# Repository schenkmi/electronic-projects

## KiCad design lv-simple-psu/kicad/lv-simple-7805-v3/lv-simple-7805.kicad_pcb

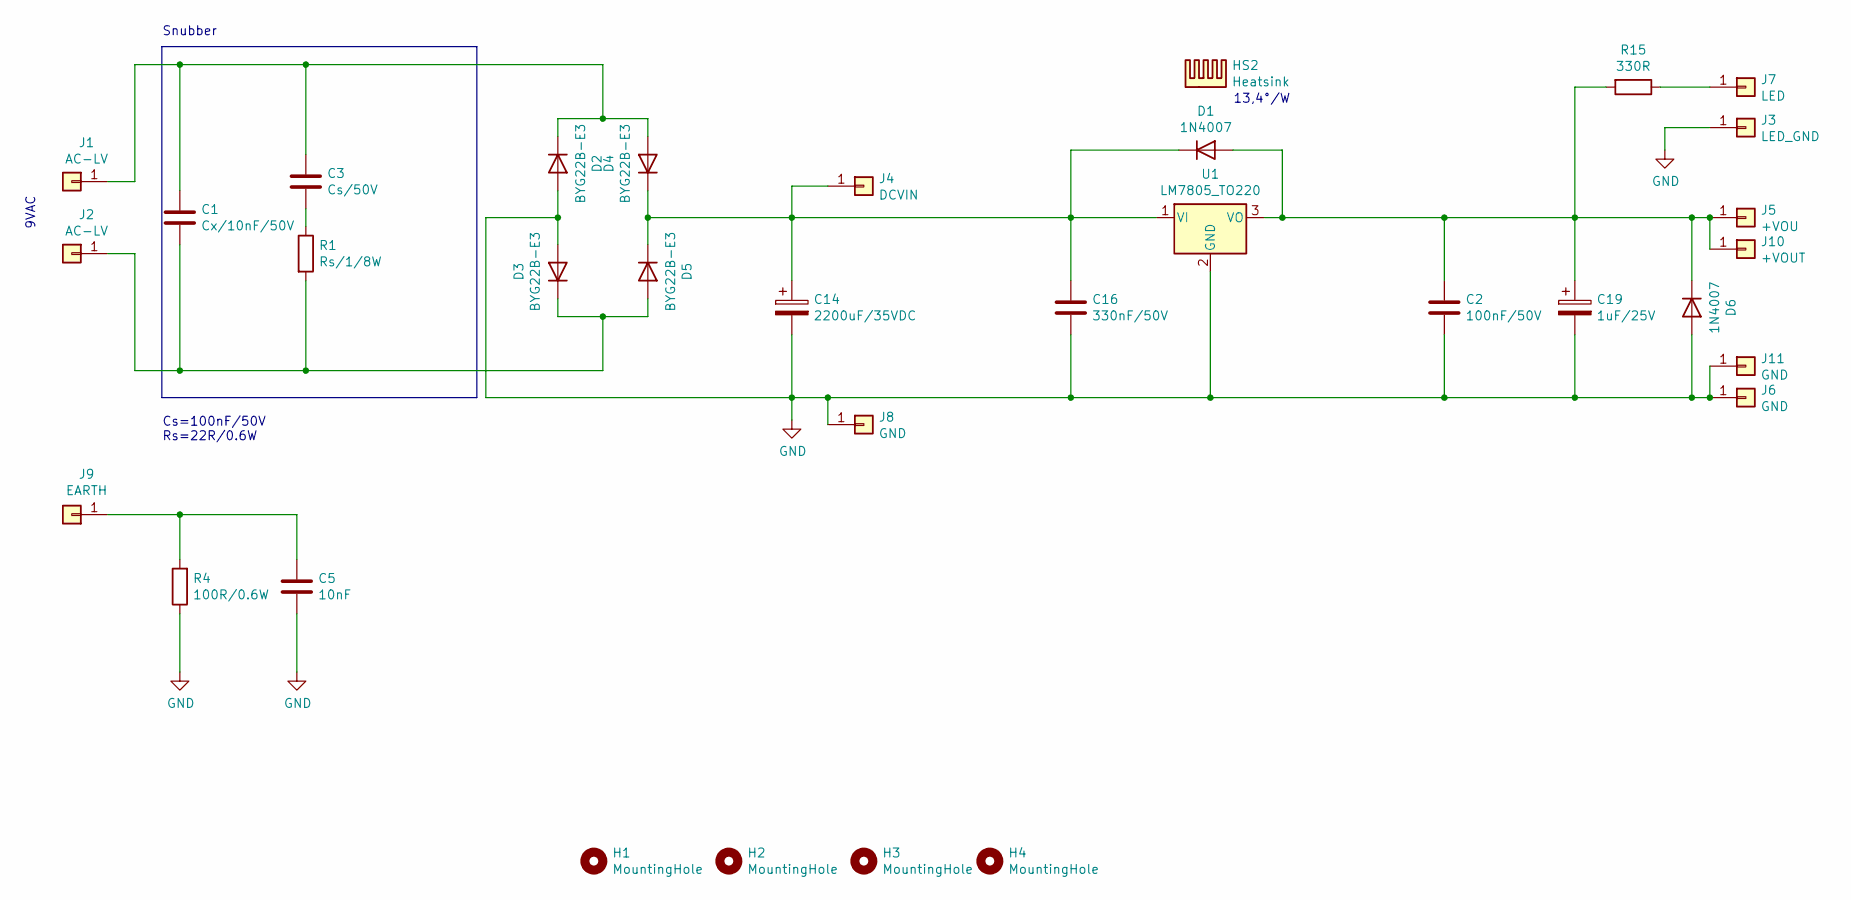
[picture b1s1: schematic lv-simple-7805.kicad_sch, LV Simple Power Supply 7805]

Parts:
C1: Cx/10nF/50V; C_0805_2012Metric_Pad1.18x1.45mm_HandSolder
C2: 100nF/50V; C_0805_2012Metric_Pad1.18x1.45mm_HandSolder
C3: Cs/50V; C_0805_2012Metric_Pad1.18x1.45mm_HandSolder
C5: 10nF; C_Rect_L7.2mm_W2.5mm_P5.00mm_FKS2_FKP2_MKS2_MKP2
C14: 2200uF/35VDC; CP_Radial_D16.0mm_P7.50mm
C16: 330nF/50V; C_0805_2012Metric_Pad1.18x1.45mm_HandSolder
C19: 1uF/25V; CP_Radial_D5.0mm_P2.00mm
D1, D6: 1N4007; D_SMA_Handsoldering
D2, D3, D4, D5: BYG22B-E3; D_SMA_Handsoldering
H1, H2, H3, H4: MountingHole; MountingHole_3.2mm_M3
HS2: Heatsink; Heatsink_Fischer_SK104-STC-STIC_35x13mm_2xDrill2.5mm
J1, J2: AC-LV; Pin_D1.3mm_L11.0mm
J3: LED_GND; Pin_D1.0mm_L10.0mm
J4: DCVIN; Pin_D1.3mm_L11.0mm
J5: +VOU; Pin_D1.3mm_L11.0mm
J6, J8: GND; Pin_D1.3mm_L11.0mm
J7: LED; Pin_D1.0mm_L10.0mm
J9: EARTH; Pin_D1.3mm_L11.0mm
J10: +VOUT; Pin_D1.0mm_L10.0mm
J11: GND; Pin_D1.0mm_L10.0mm
R1: Rs/1/8W; R_0805_2012Metric_Pad1.20x1.40mm_HandSolder
R4: 100R/0.6W; R_Axial_DIN0207_L6.3mm_D2.5mm_P10.16mm_Horizontal
R15: 330R; R_0805_2012Metric_Pad1.20x1.40mm_HandSolder
U1: LM7805_TO220; TO-220-3_Vertical

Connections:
GND: C2.2, C5.2, C14.2, C16.2, C19.2, D2.2 (A), D3.2 (A), D6.2 (A), J3.1, J6.1, J8.1, J11.1, R4.1, U1.2 (GND)
unnamed: C1.1, C3.1, D2.1 (K), D4.2 (A), J1.1
unnamed: C1.2, D3.1 (K), D5.2 (A), J2.1, R1.2
unnamed: C3.2, R1.1
unnamed: C5.1, J9.1, R4.2
unnamed: C14.1, C16.1, D1.1 (K), D4.1 (K), D5.1 (K), J4.1, U1.1 (VI)
unnamed: C2.1, C19.1, D1.2 (A), D6.1 (K), J5.1, J10.1, R15.2, U1.3 (VO)
unnamed: J7.1, R15.1

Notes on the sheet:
Snubber
9VAC
13,4°/W
Cs=100nF/50V Rs=22R/0.6W

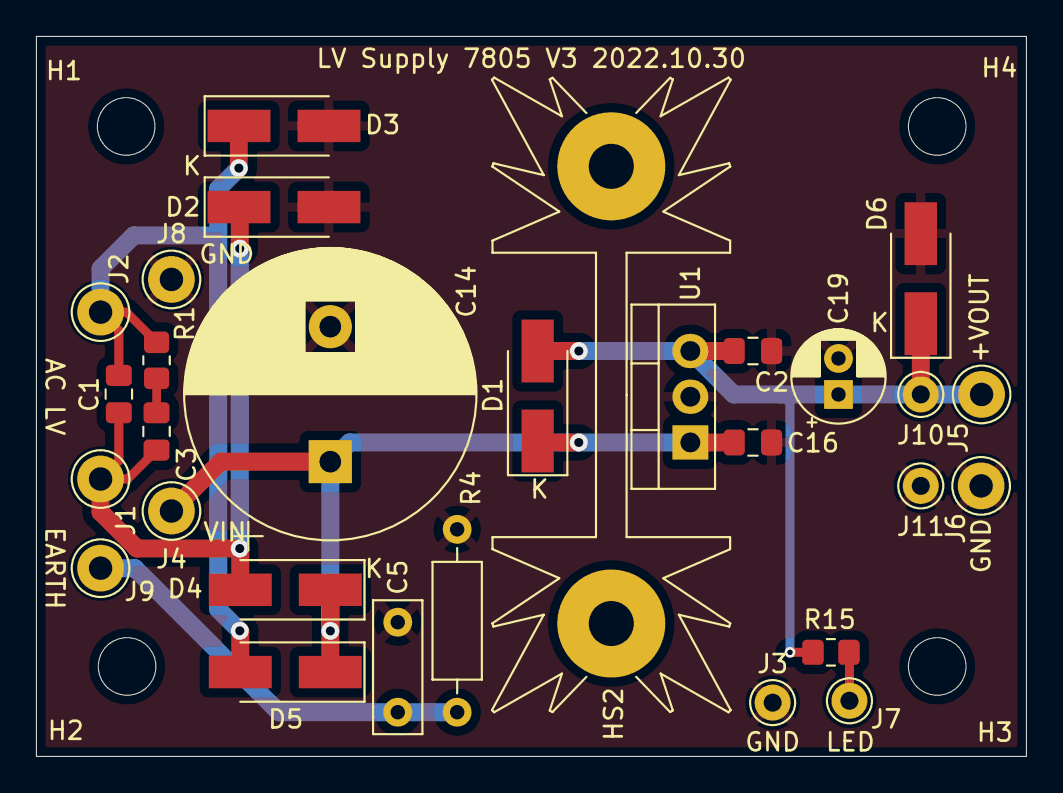
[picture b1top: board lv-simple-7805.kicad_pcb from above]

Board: 2 copper layers, 55.0 x 40.0 mm, 33 parts (0 on the bottom side), 8 nets.

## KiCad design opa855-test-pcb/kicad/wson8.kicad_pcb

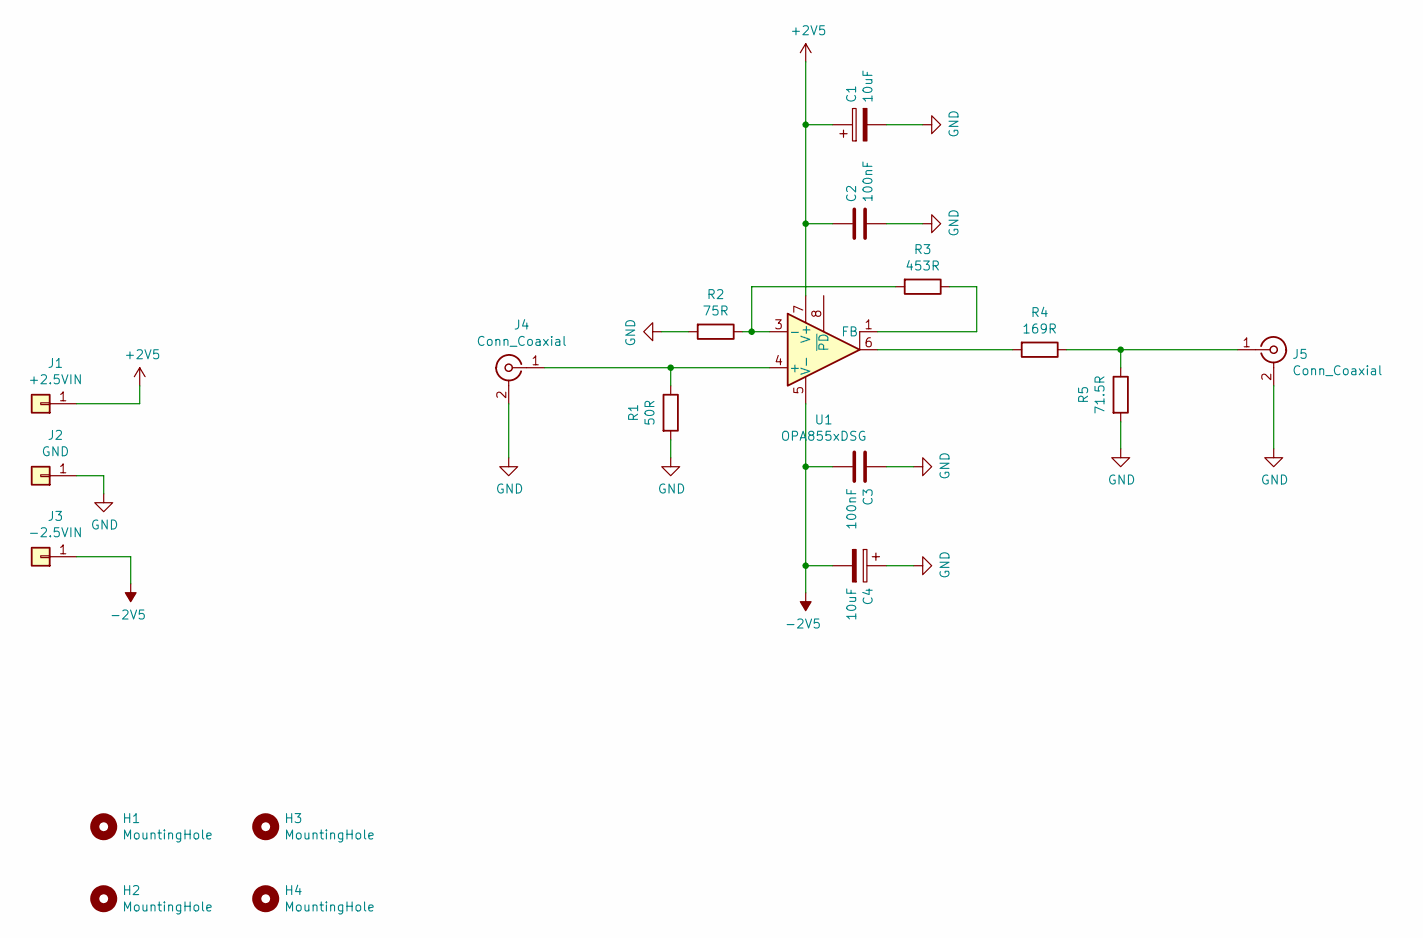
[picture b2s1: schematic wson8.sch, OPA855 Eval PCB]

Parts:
C1, C4: 10uF; CP_EIA-3528-21_Kemet-B_Pad1.50x2.35mm_HandSolder
C2, C3: 100nF; C_0603_1608Metric_Pad1.08x0.95mm_HandSolder
H1, H2, H3, H4: MountingHole; MountingHole_3.2mm_M3
J1: +2.5VIN; Pin_D1.0mm_L10.0mm
J2: GND; Pin_D1.0mm_L10.0mm
J3: -2.5VIN; Pin_D1.0mm_L10.0mm
J4, J5: Conn_Coaxial; MMCX_Molex_73415-1471_Vertical
R1: 50R; R_0603_1608Metric_Pad0.98x0.95mm_HandSolder
R2: 75R; R_0603_1608Metric_Pad0.98x0.95mm_HandSolder
R3: 453R; R_0603_1608Metric_Pad0.98x0.95mm_HandSolder
R4: 169R; R_0603_1608Metric_Pad0.98x0.95mm_HandSolder
R5: 71.5R; R_0603_1608Metric_Pad0.98x0.95mm_HandSolder
U1: OPA855xDSG; WSON-8-1EP_2x2mm_P0.5mm_EP0.9x1.6mm

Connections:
+2V5: C1.1, C2.1, J1.1, U1.7 (V+)
-2V5: C3.2, C4.2, J3.1, U1.5 (V-), U1.9 (V-)
GND: C1.2, C2.2, C3.1, C4.1, J2.1, J4.2 (Ext), J5.2 (Ext), R1.2, R2.2, R5.2
unnamed: J4.1 (In), R1.1, U1.4 (+)
unnamed: J5.1 (In), R4.1, R5.1
unnamed: R2.1, R3.2, U1.3 (-)
unnamed: R3.1, U1.1 (FB)
unnamed: R4.2, U1.6

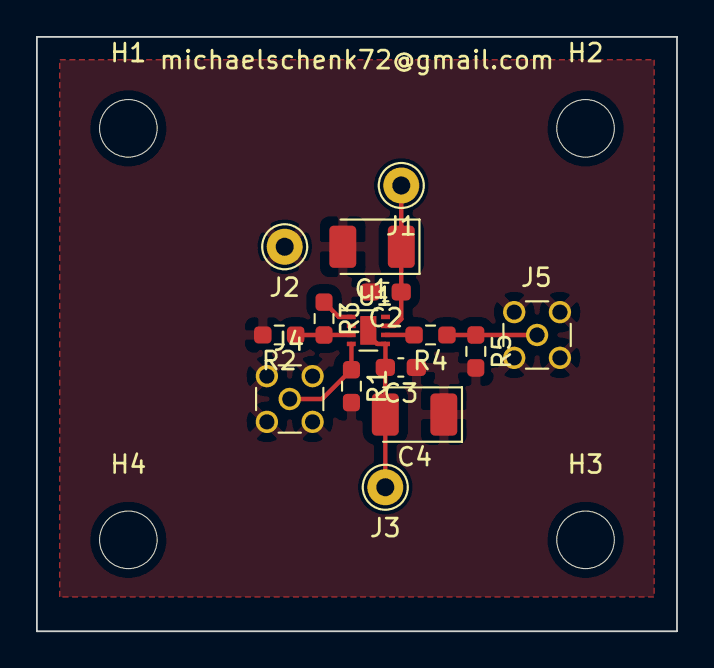
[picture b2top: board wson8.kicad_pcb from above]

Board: 2 copper layers, 35.6 x 33.0 mm, 19 parts (0 on the bottom side), 8 nets.

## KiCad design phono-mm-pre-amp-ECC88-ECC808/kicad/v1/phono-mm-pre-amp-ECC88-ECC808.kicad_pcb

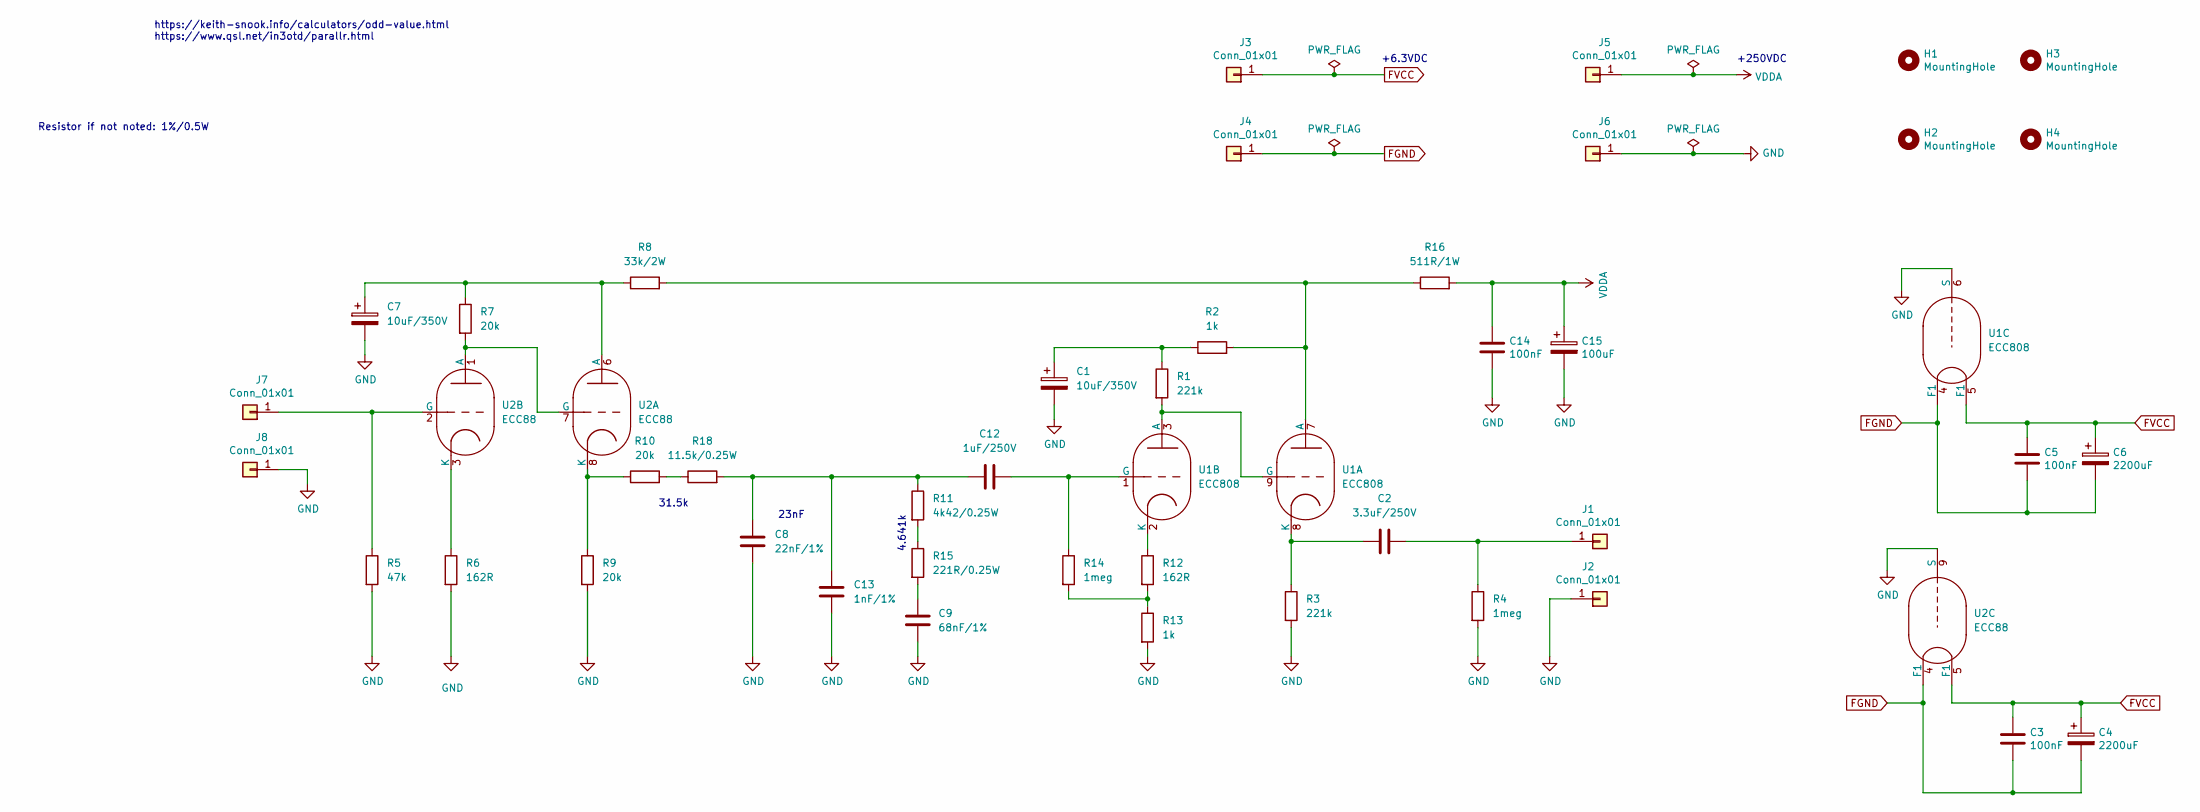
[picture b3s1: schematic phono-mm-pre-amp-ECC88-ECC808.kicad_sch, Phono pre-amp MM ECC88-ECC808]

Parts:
C1, C7: 10uF/350V; CP_Radial_D10.0mm_P5.00mm
C2: 3.3uF/250V; C_Rect_L31.5mm_W13.0mm_P27.50mm_MKS4
C3, C5: 100nF; C_Rect_L7.2mm_W2.5mm_P5.00mm_FKS2_FKP2_MKS2_MKP2
C4, C6: 2200uF; CP_Radial_D16.0mm_P7.50mm
C8: 22nF/1%; C_Rect_L7.2mm_W5.5mm_P5.00mm_FKS2_FKP2_MKS2_MKP2
C9: 68nF/1%; C_Rect_L7.2mm_W7.2mm_P5.00mm_FKS2_FKP2_MKS2_MKP2
C12: 1uF/250V; C_Rect_L26.5mm_W11.5mm_P22.50mm_MKS4
C13: 1nF/1%; C_Rect_L7.2mm_W5.5mm_P5.00mm_FKS2_FKP2_MKS2_MKP2
C14: 100nF; C_Rect_L16.5mm_W5.0mm_P15.00mm_MKT
C15: 100uF; CP_Radial_D18.0mm_P7.50mm
H1, H2, H3, H4: MountingHole; MountingHole_3.2mm_M3_Pad_Via
J1, J2, J7, J8: Conn_01x01; Pin_D1.0mm_L10.0mm
J3, J4, J5, J6: Conn_01x01; Pin_D1.3mm_L11.0mm
R1, R3: 221k; R_Axial_DIN0207_L6.3mm_D2.5mm_P10.16mm_Horizontal
R2, R13: 1k; R_Axial_DIN0207_L6.3mm_D2.5mm_P10.16mm_Horizontal
R4, R14: 1meg; R_Axial_DIN0207_L6.3mm_D2.5mm_P10.16mm_Horizontal
R5: 47k; R_Axial_DIN0207_L6.3mm_D2.5mm_P10.16mm_Horizontal
R6, R12: 162R; R_Axial_DIN0207_L6.3mm_D2.5mm_P10.16mm_Horizontal
R7, R9, R10: 20k; R_Axial_DIN0207_L6.3mm_D2.5mm_P10.16mm_Horizontal
R8: 33k/2W; R_Axial_DIN0414_L11.9mm_D4.5mm_P15.24mm_Horizontal
R11: 4k42/0.25W; R_Axial_DIN0207_L6.3mm_D2.5mm_P10.16mm_Horizontal
R15: 221R/0.25W; R_Axial_DIN0207_L6.3mm_D2.5mm_P10.16mm_Horizontal
R16: 511R/1W; R_Axial_DIN0207_L6.3mm_D2.5mm_P10.16mm_Horizontal
R18: 11.5k/0.25W; R_Axial_DIN0207_L6.3mm_D2.5mm_P10.16mm_Horizontal
U1: ECC808; TubeNoval-ECC88
U2: ECC88; TubeNoval-ECC88

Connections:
FGND: C3.2, C4.2, C5.2, C6.2, J4.1, U1.4 (F1), U2.4 (F1)
FVCC: C3.1, C4.1, C5.1, C6.1, J3.1, U1.5 (F1), U2.5 (F1)
GND: C1.2, C7.2, C8.1, C9.1, C13.1, C14.2, C15.2, J2.1, J6.1, J8.1, R3.2, R4.2, R5.2, R6.2, R9.2, R13.2, U1.6 (S), U2.9 (S)
unnamed: C1.1, R1.1, R2.1
unnamed: C9.2, R15.2
unnamed: C8.2, C12.1, C13.2, R11.1, R18.2
unnamed: C2.2, J1.1, R4.1
unnamed: J7.1, R5.1, U2.2 (G)
unnamed: R10.2, R18.1
unnamed: R11.2, R15.1
unnamed: R12.2, R13.1, R14.2
unnamed: R2.2, R8.2, R16.1, U1.7 (A)
unnamed: R1.2, U1.3 (A), U1.9 (G)
unnamed: C2.1, R3.1, U1.8 (K)
unnamed: C12.2, R14.1, U1.1 (G)
unnamed: R12.1, U1.2 (K)
unnamed: C7.1, R7.1, R8.1, U2.6 (A)
unnamed: R7.2, U2.1 (A), U2.7 (G)
unnamed: R9.1, R10.1, U2.8 (K)
unnamed: R6.1, U2.3 (K)
VDDA: C14.1, C15.1, J5.1, R16.2

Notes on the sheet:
23nF
+250VDC
4.641k
Resistor if not noted: 1%/0.5W
31.5k
https://keith-snook.info/calculators/odd-value.html https://www.qsl.net/in3otd/parallr.html
+6.3VDC

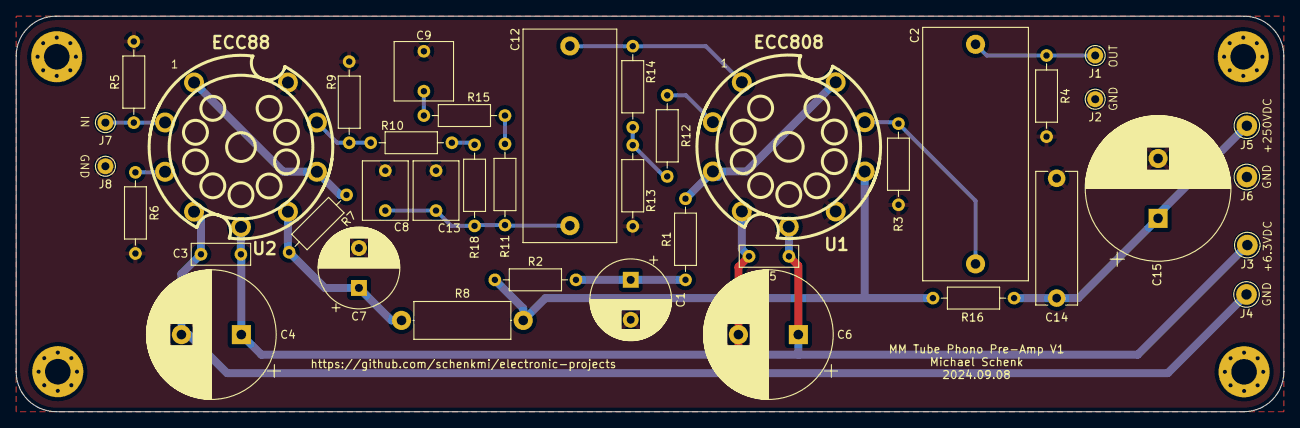
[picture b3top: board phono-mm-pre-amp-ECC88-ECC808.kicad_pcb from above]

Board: 2 copper layers, 158.8 x 49.5 mm, 44 parts (0 on the bottom side), 21 nets.

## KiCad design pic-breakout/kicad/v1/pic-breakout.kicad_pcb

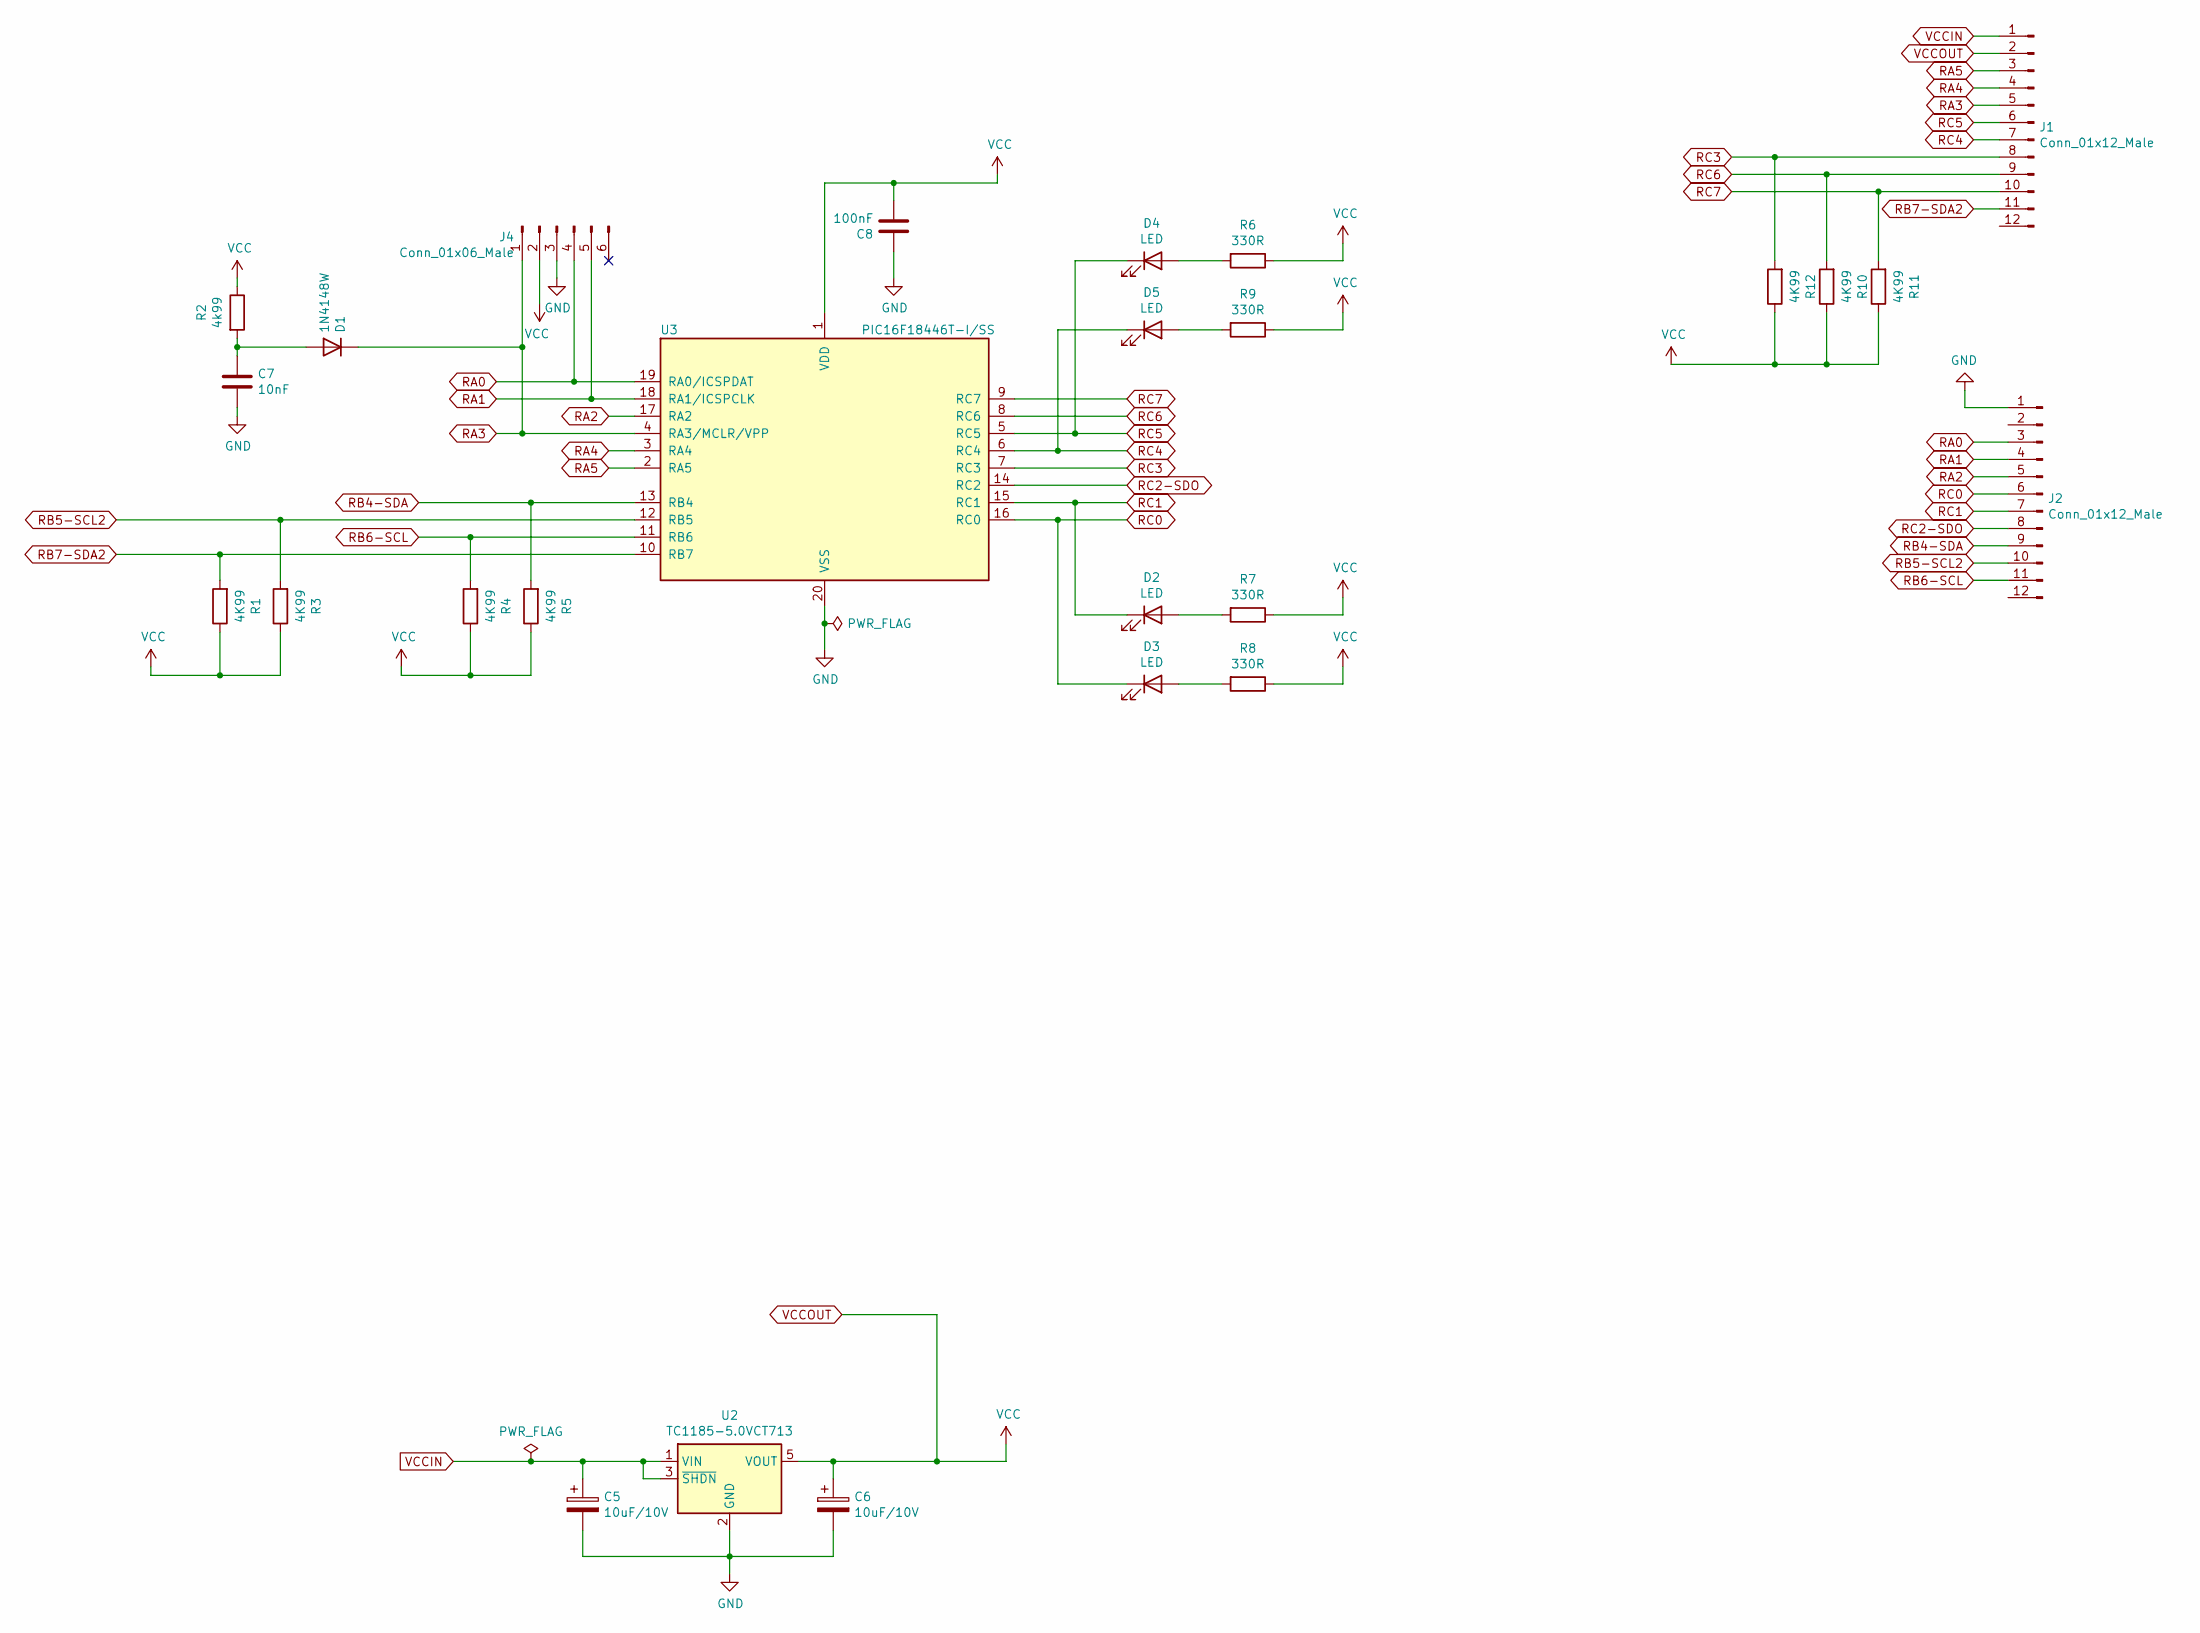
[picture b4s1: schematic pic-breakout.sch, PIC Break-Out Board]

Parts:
C5, C6: 10uF/10V; CP_EIA-2012-15_AVX-P_Pad1.30x1.05mm_HandSolder
C7: 10nF; C_0603_1608Metric_Pad1.08x0.95mm_HandSolder
C8: 100nF; C_0603_1608Metric_Pad1.08x0.95mm_HandSolder
D1: 1N4148W; D_SOD-123
D2, D3, D4, D5: LED; LED_0805_2012Metric_Pad1.15x1.40mm_HandSolder
J1, J2: Conn_01x12_Male; PinHeader_1x12_P2.54mm_Vertical
J4: Conn_01x06_Male; PinHeader_1x06_P2.54mm_Vertical
R1, R3, R4, R5, R10, R11, R12: 4K99; R_0603_1608Metric_Pad0.98x0.95mm_HandSolder
R2: 4k99; R_0603_1608Metric_Pad0.98x0.95mm_HandSolder
R6, R7, R8, R9: 330R; R_0603_1608Metric_Pad0.98x0.95mm_HandSolder
U2: TC1185-5.0VCT713; SOT-23-5
U3: PIC16F18446T-I/SS; SSOP-20_5.3x7.2mm_P0.65mm

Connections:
GND: C5.2, C6.2, C7.2, C8.1, J2.1, J4.3, U2.2 (GND), U3.20 (VSS)
unnamed: C7.1, D1.2 (A), R2.2
unnamed: D2.2 (A), R7.2
unnamed: D3.2 (A), R8.2
unnamed: D4.2 (A), R6.2
unnamed: D5.2 (A), R9.2
RA0: J2.3, J4.4, U3.19 (RA0/ICSPDAT)
RA1: J2.4, J4.5, U3.18 (RA1/ICSPCLK)
RA2: J2.5, U3.17 (RA2)
RA3: D1.1 (K), J1.5, J4.1, U3.4 (RA3/MCLR/VPP)
RA4: J1.4, U3.3 (RA4)
RA5: J1.3, U3.2 (RA5)
RB4-SDA: J2.9, R5.2, U3.13 (RB4)
RB5-SCL2: J2.10, R3.2, U3.12 (RB5)
RB6-SCL: J2.11, R4.2, U3.11 (RB6)
RB7-SDA2: J1.11, R1.2, U3.10 (RB7)
RC0: D3.1 (K), J2.6, U3.16 (RC0)
RC1: D2.1 (K), J2.7, U3.15 (RC1)
RC2-SDO: J2.8, U3.14 (RC2)
RC3: J1.8, R12.2, U3.7 (RC3)
RC4: D5.1 (K), J1.7, U3.6 (RC4)
RC5: D4.1 (K), J1.6, U3.5 (RC5)
RC6: J1.9, R10.2, U3.8 (RC6)
RC7: J1.10, R11.2, U3.9 (RC7)
VCCIN: C5.1, J1.1, U2.1 (VIN), U2.3 (~SHDN)
VCCOUT: C6.1, C8.2, J1.2, J4.2, R1.1, R2.1, R3.1, R4.1, R5.1, R6.1, R7.1, R8.1, R9.1, R10.1, R11.1, R12.1, U2.5 (VOUT), U3.1 (VDD)

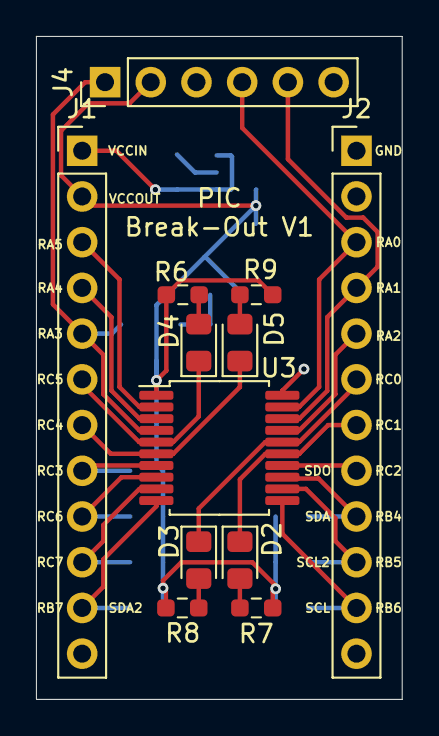
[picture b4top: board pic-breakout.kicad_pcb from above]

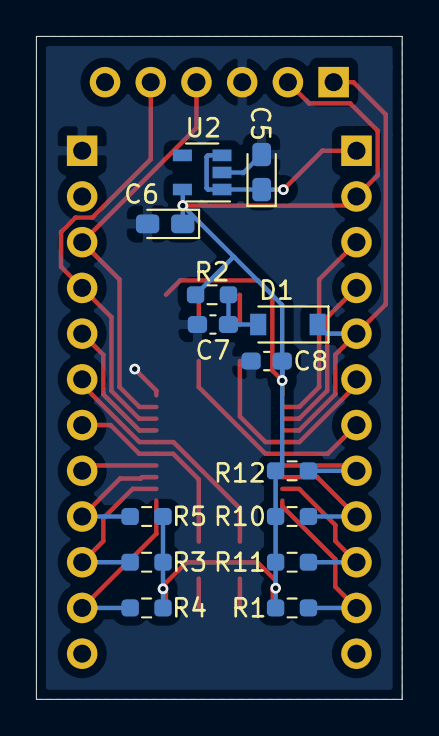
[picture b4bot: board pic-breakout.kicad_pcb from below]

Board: 2 copper layers, 20.3 x 36.8 mm, 26 parts (14 on the bottom side), 26 nets.
